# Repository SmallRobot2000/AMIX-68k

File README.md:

# AMIX-68k
This is my Motorola 68010 CPU based system.
I plan to make it with 68010 CPU @ 12Mhz, DMA(68450) and othere periferials @ 10Mhz, IDE disk (CF card or good old HDD), Video output (Xosera), Aduio output (Aslo Xosera), Timers (again Xosera and 68230), Keyboard (68230 with RC2014 Yellow series MSX style keyboard), UART (16550 @ 115200 bps)

This isn't my first or (hopefully)last Retro style computer system, I alredy made two 6502 based computers, 8088 based system that is IBM compatable with 8 bit ISA, and built and coded for a handfull of z80/z180 based systems, mostly two RC2014 (Its funny that i like z80 MUCH more than 6502 but never made a system araund z80).
And also have ZX Spectrum 48k and ZX Spectrum NEXT.

But somehow this is the first time working with 68k chip, I known for 68k style systems but was afraid to touch them because they are two times more complex thatn 8 bit(right?) especely when i made 8088 system that was 8/16 bit and coudnt think how complecated would a full 16 bit system be, but when i looked closer at Motorola 68000 i thought i steped in to heven because of all the documentation and datasheet, and how a SINGLE datasheet was enough to understand almost everything to know(looking at you Intel).

# SPECS

|CPU | Motorola 68010 @ 12Mhz|
|----|-----------------------|
|RAM | 2 MB SRAM (Maybe DRAM in future)
|DMA | 68450 @ 10 Mhz|
|VIDEO & AUDIO| Xosera 640x480 2 playfields and Copper ( ͡❛ ͜ʖ ͡❛)|
|Keyboard| RC2014 Yellow series MSX style keyboard with n key rollover|
|DISK| IDE interface CF card or clasic HDD|
|UART| 16550 @ 18.432 Mhz -> 115200 bps|
|POWER| ATX PSU or 12V in|
|TIME & TIMERS| Tmers in Xosera and 68230, and RTC (SparkFun BOB-10160)|

# Present
All important stuff in kernel is done, now its time to make a unix like shell inside the kernel, later I will make it a executable file
All executables are in ELF file format, scripts are not yet suported nether are pipes and redirects.
# Future (TODO)

 - Add working permissions and thus users
 - Shell as executable not built in kenrel
 - Support for pipes and redirects
 - Move keyboard to a new process and make it all in C because now it sometimes glitches
 - Clean up code and make more flexiable(cariables insted of defines)
 - Move some stuff to files like history and $PATH etc.
 - Add global sbrk with suport for freeing all alocations per process when killed
 - When poritng keyboard to C add some shortcuts
 - add system specific command something similar to symctl
 - add Ethernet as expantion

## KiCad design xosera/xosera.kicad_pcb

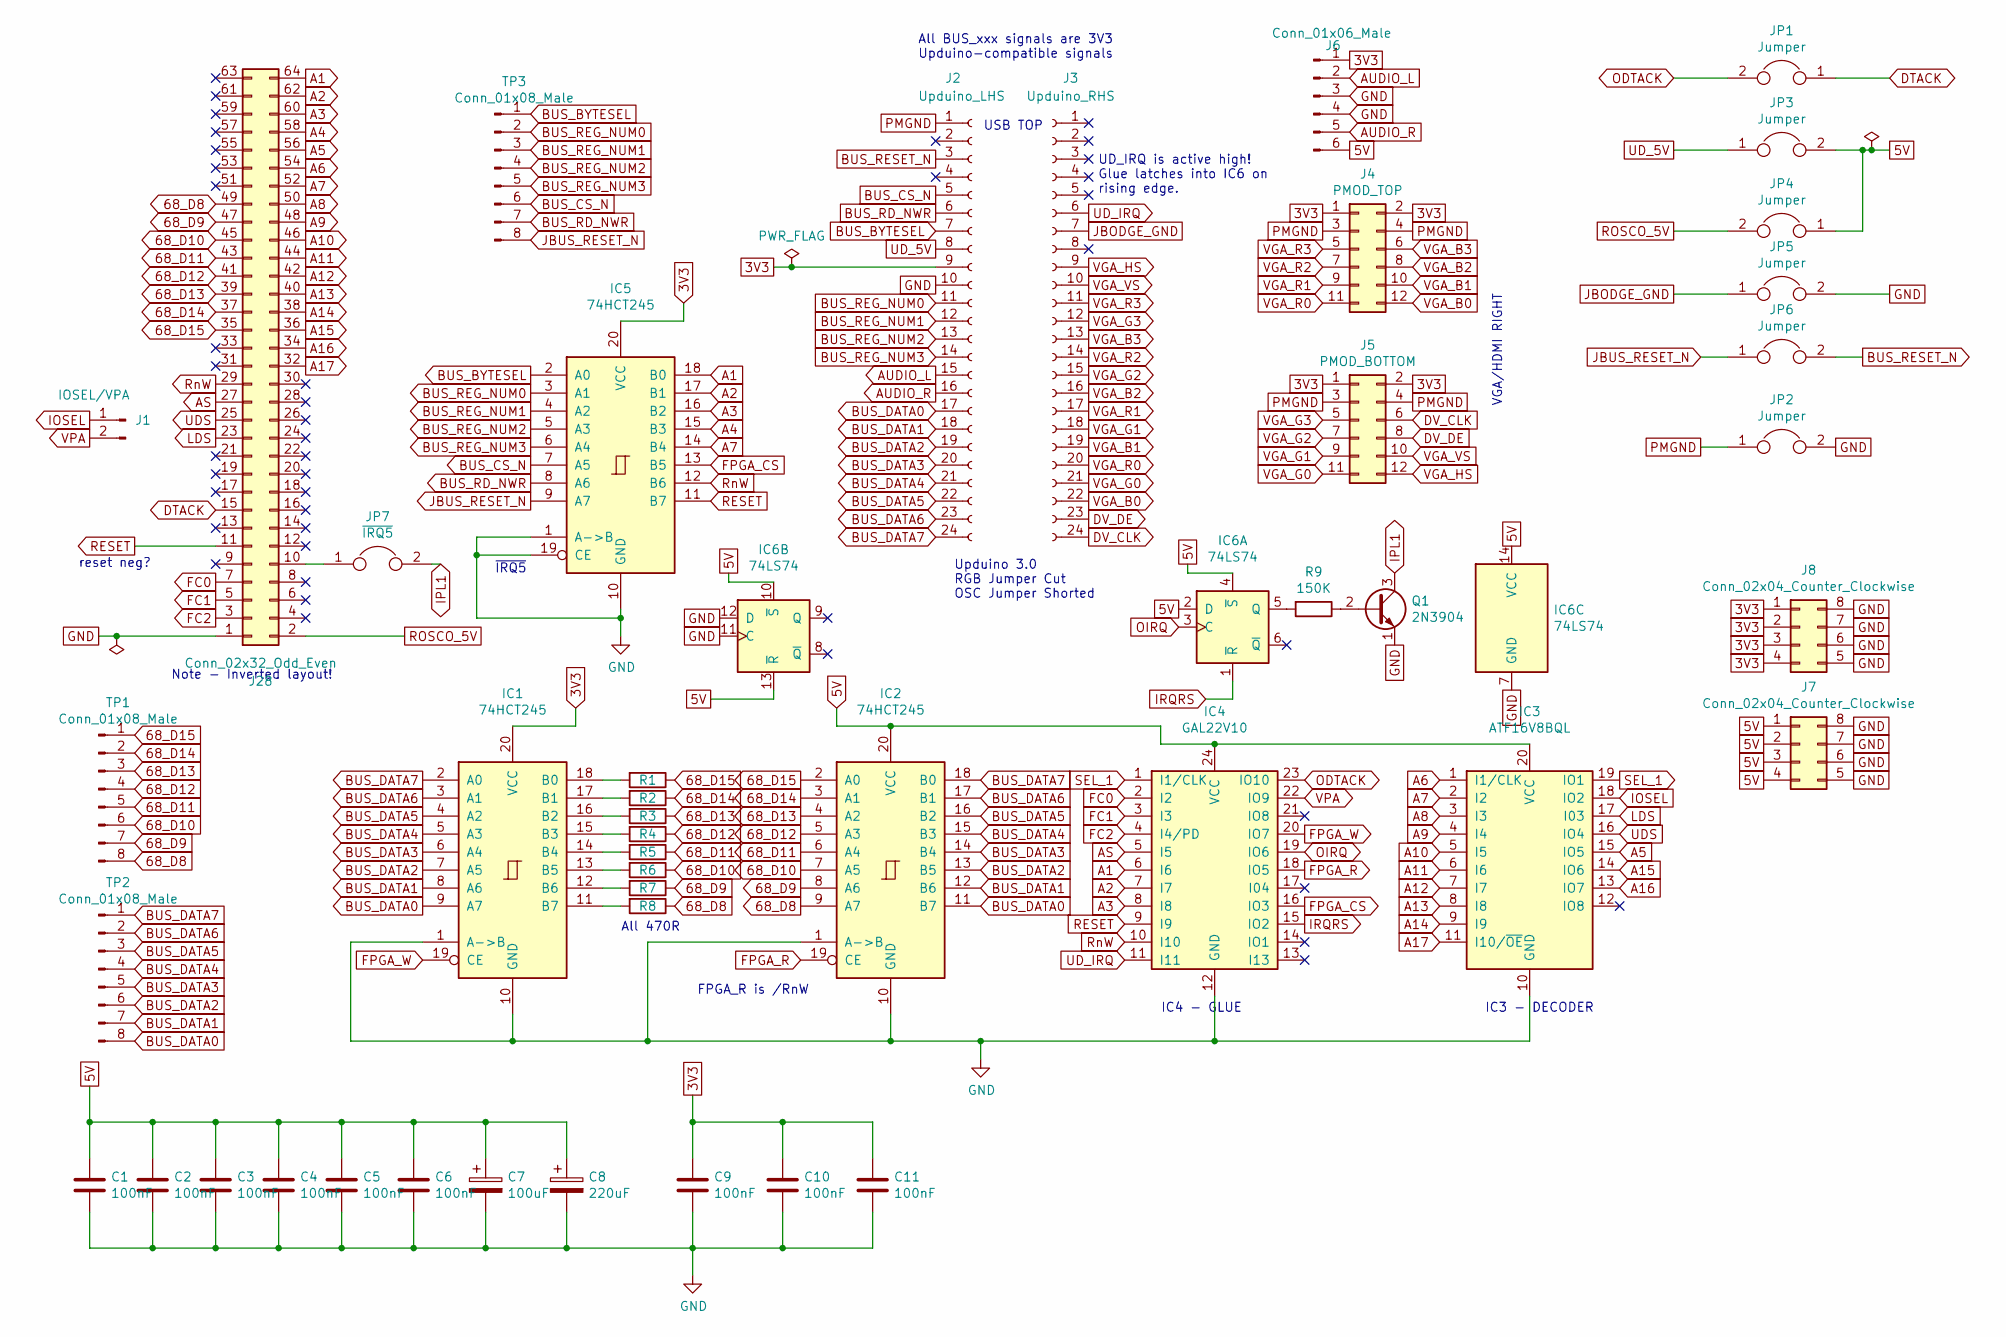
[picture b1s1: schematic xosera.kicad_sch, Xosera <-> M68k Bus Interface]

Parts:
C1, C2, C3, C4, C5, C6, C9, C10, C11: 100nF; C2.5-3
C7: 100uF; CP_Radial_D5.0mm_P2.50mm
C8: 220uF; CP_Radial_D6.3mm_P2.50mm
IC1, IC2, IC5: 74HCT245; DIP-20_W7.62mm_Socket_LongPads
IC3: ATF16V8BQL; DIP-20_W7.62mm_Socket_LongPads
IC4: GAL22V10; DIP-24_W7.62mm_LongPads
IC6: 74LS74; DIP-14_W7.62mm_Socket_LongPads
J1: IOSEL/VPA; PinHeader_1x02_P2.54mm_Vertical
J2: Upduino_LHS; PinSocket_1x24_P2.54mm_Vertical
J3: Upduino_RHS; PinSocket_1x24_P2.54mm_Vertical
J4: PMOD_TOP; PinSocket_2x06_P2.54mm_Horizontal
J5: PMOD_BOTTOM; PinSocket_2x06_P2.54mm_Horizontal
J6: Conn_01x06_Male; PinHeader_1x06_P2.54mm_Vertical
J7, J8: Conn_02x04_Counter_Clockwise; PinHeader_2x04_P2.54mm_Vertical
J28: Conn_02x32_Odd_Even; PinSocket_2x32_P2.54mm_Horizontal
JP1, JP3, JP4, JP5, JP6: Jumper; PinHeader_1x02_P2.54mm_Vertical
JP2: Jumper; SolderJumper-2_P1.3mm_Open_Pad1.0x1.5mm
JP7: ~{IRQ5}; SolderJumper-2_P1.3mm_Open_Pad1.0x1.5mm
Q1: 2N3904; TO-92_HandSolder
R1, R2, R3, R4, R5, R6, R7, R8: R; R-0207_10
R9: 150K; R-0207_10
TP1, TP2, TP3: Conn_01x08_Male; PinHeader_1x08_P2.54mm_Vertical

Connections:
3V3: C9.1, C10.1, C11.1, IC1.20 (VCC), IC5.20 (VCC), J2.9, J4.1, J4.2, J5.1, J5.2, J6.1, J8.1, J8.2, J8.3, J8.4
68_D8: IC2.9 (A7), J28.49, R8.1, TP1.8
68_D9: IC2.8 (A6), J28.47, R7.1, TP1.7
68_D10: IC2.7 (A5), J28.45, R6.1, TP1.6
68_D11: IC2.6 (A4), J28.43, R5.1, TP1.5
68_D12: IC2.5 (A3), J28.41, R4.1, TP1.4
68_D13: IC2.4 (A2), J28.39, R3.1, TP1.3
68_D14: IC2.3 (A1), J28.37, R2.1, TP1.2
68_D15: IC2.2 (A0), J28.35, R1.1, TP1.1
A1: IC4.6 (I6), IC5.18 (B0), J28.64
A2: IC4.7 (I7), IC5.17 (B1), J28.62
A3: IC4.8 (I8), IC5.16 (B2), J28.60
A4: IC5.15 (B3), J28.58
A5: IC3.15 (IO5), J28.56
A6: IC3.1 (I1/CLK), J28.54
A7: IC3.2 (I2), IC5.14 (B4), J28.52
A8: IC3.3 (I3), J28.50
A9: IC3.4 (I4), J28.48
A10: IC3.5 (I5), J28.46
A11: IC3.6 (I6), J28.44
A12: IC3.7 (I7), J28.42
A13: IC3.8 (I8), J28.40
A14: IC3.9 (I9), J28.38
A15: IC3.14 (IO6), J28.36
A16: IC3.13 (IO7), J28.34
A17: IC3.11 (I10/~OE), J28.32
AS: IC4.5 (I5), J28.27
AUDIO_L: J2.15, J6.2
AUDIO_R: J2.16, J6.5
BUS_BYTESEL: IC5.2 (A0), J2.7, TP3.1
BUS_CS_N: IC5.7 (A5), J2.5, TP3.6
BUS_DATA0: IC1.9 (A7), IC2.11 (B7), J2.17, TP2.8
BUS_DATA1: IC1.8 (A6), IC2.12 (B6), J2.18, TP2.7
BUS_DATA2: IC1.7 (A5), IC2.13 (B5), J2.19, TP2.6
BUS_DATA3: IC1.6 (A4), IC2.14 (B4), J2.20, TP2.5
BUS_DATA4: IC1.5 (A3), IC2.15 (B3), J2.21, TP2.4
BUS_DATA5: IC1.4 (A2), IC2.16 (B2), J2.22, TP2.3
BUS_DATA6: IC1.3 (A1), IC2.17 (B1), J2.23, TP2.2
BUS_DATA7: IC1.2 (A0), IC2.18 (B0), J2.24, TP2.1
BUS_RD_NWR: IC5.8 (A6), J2.6, TP3.7
BUS_REG_NUM0: IC5.3 (A1), J2.11, TP3.2
BUS_REG_NUM1: IC5.4 (A2), J2.12, TP3.3
BUS_REG_NUM2: IC5.5 (A3), J2.13, TP3.4
BUS_REG_NUM3: IC5.6 (A4), J2.14, TP3.5
BUS_RESET_N: J2.3, JP6.2
DTACK: J28.15, JP1.1
DV_CLK: J3.24, J5.6
DV_DE: J3.23, J5.8
FC0: IC4.2 (I2), J28.7
FC1: IC4.3 (I3), J28.5
FC2: IC4.4 (I4/PD), J28.3
FPGA_CS: IC4.16 (IO3), IC5.13 (B5)
FPGA_R: IC2.19 (CE), IC4.18 (IO5)
FPGA_W: IC1.19 (CE), IC4.20 (IO7)
IOSEL: IC3.18 (IO2), J1.1
IPL1: JP7.2, Q1.3 (C)
IRQRS: IC4.15 (IO2), IC6.1 (~R)
JBODGE_GND: J3.7, JP5.1
JBUS_RESET_N: IC5.9 (A7), JP6.1, TP3.8
LDS: IC3.17 (I03), J28.23
unnamed: IC1.18 (B0), R1.2
unnamed: IC1.17 (B1), R2.2
unnamed: IC1.16 (B2), R3.2
unnamed: IC1.15 (B3), R4.2
unnamed: IC1.14 (B4), R5.2
unnamed: IC1.13 (B5), R6.2
unnamed: IC1.12 (B6), R7.2
unnamed: IC1.11 (B7), R8.2
unnamed: IC6.5 (Q), R9.2
unnamed: J28.10, JP7.1
unnamed: Q1.2 (B), R9.1
ODTACK: IC4.23 (IO10), JP1.2
OIRQ: IC4.19 (IO6), IC6.3 (C)
PMGND: J2.1, J4.3, J4.4, J5.3, J5.4, JP2.1
RESET: IC4.9 (I9), IC5.11 (B7), J28.11
ROSCO_5V: J28.2, JP4.2
RnW: IC4.10 (I10), IC5.12 (B6), J28.29
SEL_1: IC3.19 (IO1), IC4.1 (I1/CLK)
UDS: IC3.16 (IO4), J28.25
UD_5V: J2.8, JP3.1
UD_IRQ: IC4.11 (I11), J3.6
VGA_B0: J3.22, J4.12
VGA_B1: J3.19, J4.10
VGA_B2: J3.16, J4.8
VGA_B3: J3.13, J4.6
VGA_G0: J3.21, J5.11
VGA_G1: J3.18, J5.9
VGA_G2: J3.15, J5.7
VGA_G3: J3.12, J5.5
VGA_HS: J3.9, J5.12
VGA_R0: J3.20, J4.11
VGA_R1: J3.17, J4.9
VGA_R2: J3.14, J4.7
VGA_R3: J3.11, J4.5
VGA_VS: J3.10, J5.10
VPA: IC4.22 (IO9), J1.2

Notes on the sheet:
All BUS_xxx signals are 3V3 Upduino-compatible signals
VGA/HDMI RIGHT
~{IRQ5}
USB TOP
IC3 - DECODER
FPGA_R is /RnW
All 470R
reset neg?
Note - Inverted layout!
UD_IRQ is active high! Glue latches into IC6 on rising edge.
Upduino 3.0 RGB Jumper Cut OSC Jumper Shorted
IC4 - GLUE

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
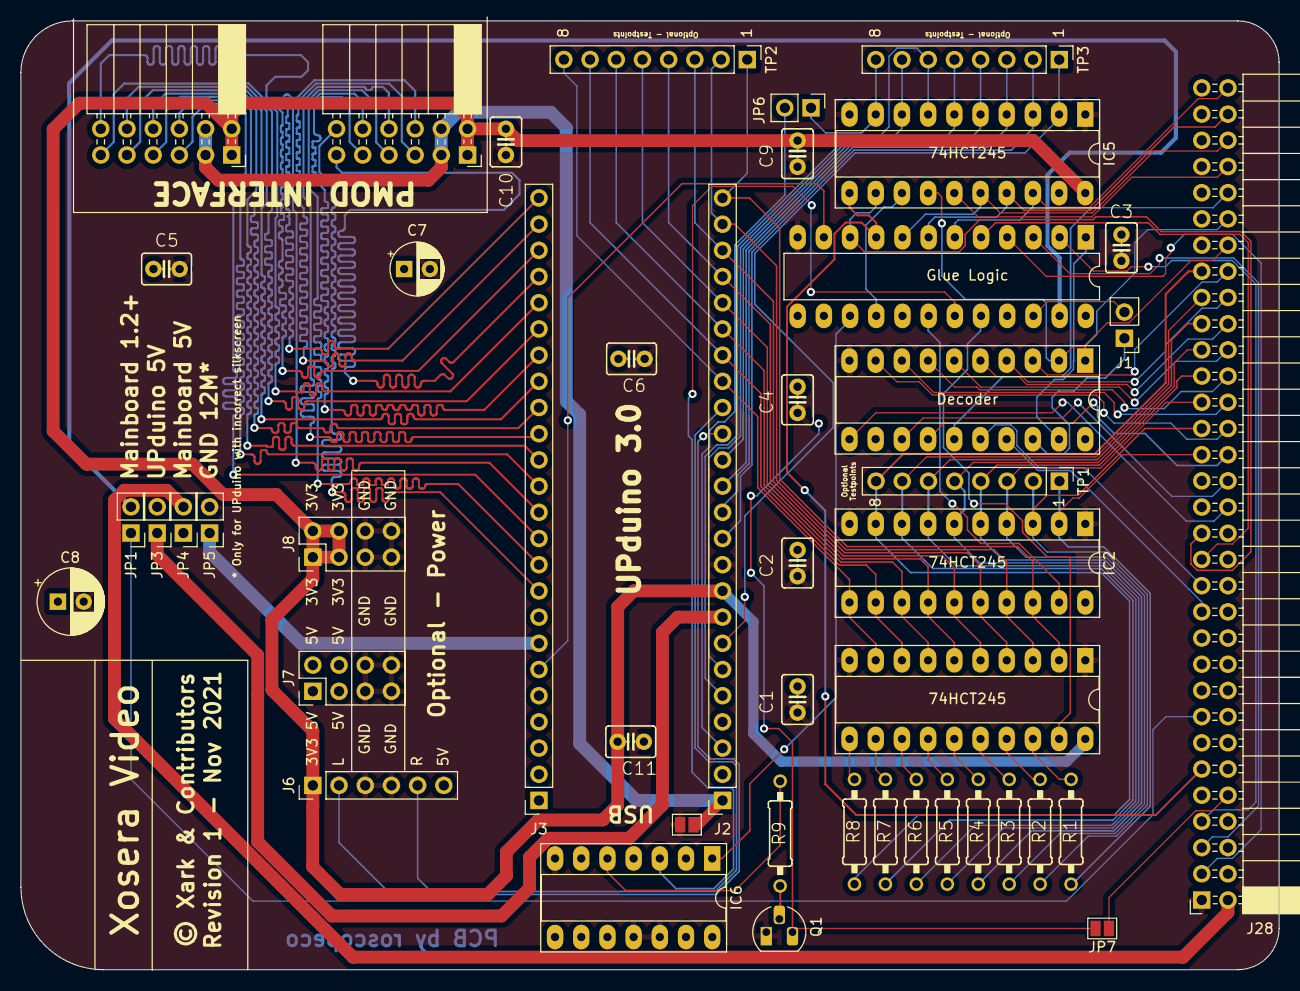
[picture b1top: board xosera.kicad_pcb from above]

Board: 4 copper layers, 122.0 x 92.0 mm, 46 parts (0 on the bottom side), 98 nets.

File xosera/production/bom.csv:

Designator,Footprint,Quantity,Value,LCSC Part #
"C1, C10, C11, C2, C3, C4, C5, C6, C9",C2.5-3,9,100nF,
C7,CP_Radial_D5.0mm_P2.50mm,1,100uF,
C8,CP_Radial_D6.3mm_P2.50mm,1,220uF,
"IC1, IC2, IC5",DIP-20_W7.62mm_Socket_LongPads,3,74HCT245,
IC3,DIP-20_W7.62mm_Socket_LongPads,1,ATF16V8BQL,
IC4,DIP-24_W7.62mm_LongPads,1,GAL22V10,
IC6,DIP-14_W7.62mm_Socket_LongPads,1,74LS74,
J1,PinHeader_1x02_P2.54mm_Vertical,1,IOSEL/VPA,
J2,PinSocket_1x24_P2.54mm_Vertical,1,Upduino_LHS,
J28,PinSocket_2x32_P2.54mm_Horizontal,1,Conn_02x32_Odd_Even,
J3,PinSocket_1x24_P2.54mm_Vertical,1,Upduino_RHS,
J4,PinSocket_2x06_P2.54mm_Horizontal,1,PMOD_TOP,
J5,PinSocket_2x06_P2.54mm_Horizontal,1,PMOD_BOTTOM,
J6,PinHeader_1x06_P2.54mm_Vertical,1,Conn_01x06_Male,
"J7, J8",PinHeader_2x04_P2.54mm_Vertical,2,Conn_02x04_Counter_Clockwise,
"JP1, JP3, JP4, JP5, JP6",PinHeader_1x02_P2.54mm_Vertical,5,Jumper,
JP2,SolderJumper-2_P1.3mm_Open_Pad1.0x1.5mm,1,Jumper,
JP7,SolderJumper-2_P1.3mm_Open_Pad1.0x1.5mm,1,~{IRQ5},
Q1,TO-92_HandSolder,1,2N3904,
"R1, R2, R3, R4, R5, R6, R7, R8",R-0207_10,8,R,
R9,R-0207_10,1,150K,
"TP1, TP2, TP3",PinHeader_1x08_P2.54mm_Vertical,3,Conn_01x08_Male,

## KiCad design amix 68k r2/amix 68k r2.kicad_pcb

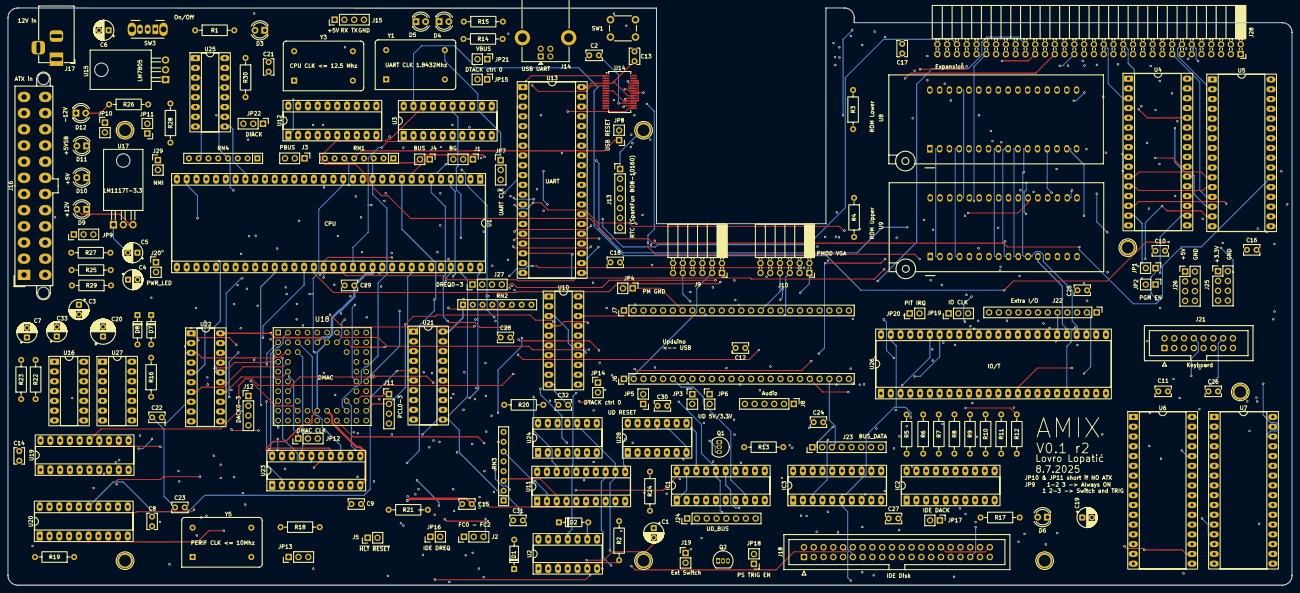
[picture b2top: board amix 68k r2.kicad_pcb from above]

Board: 4 copper layers, 333.4 x 149.9 mm, 175 parts (0 on the bottom side), 269 nets.

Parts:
C1: C_Polarized; CP_Radial_D5.0mm_P2.50mm
C2: 1uF; C_Rect_L4.0mm_W2.5mm_P2.50mm
C3, C5, C7: 10uF; CP_Radial_D5.0mm_P2.50mm
C4, C6, C33: 1uF; CP_Radial_D5.0mm_P2.50mm
C8, C9, C10, C11, C12, C13, C14, C15, C16, C17, C18, C21, C22, C23, C24, C25, C26, C27, C28, C29, C30, C31, C32: 100nF; C_Rect_L4.0mm_W2.5mm_P2.50mm
C19: 100uF; CP_Radial_D5.0mm_P2.50mm
C20: 220uF; CP_Radial_D6.3mm_P2.50mm
D1, D2: D; D_DO-35_SOD27_P7.62mm_Horizontal
D3, D4, D5, D6: LED; LED_D4.0mm
D7, D8: 1N4148; D_DO-35_SOD27_P7.62mm_Horizontal
D9: LED_+12; LED_D4.0mm
D10: LED_+5; LED_D4.0mm
D11: LED_+5SB; LED_D4.0mm
D12: LED_-12; LED_D4.0mm
HOLE1, HOLE2, HOLE3, HOLE4, HOLE5, HOLE6, HOLE7: HOLE; Hole_3mm
IC1, IC2, IC3: 74HCT245; DIP-20_W7.62mm_Socket_LongPads
J1: BG; PinHeader_1x03_P2.54mm_Vertical
J2: FCx; PinHeader_1x03_P2.54mm_Vertical
J3: PRF; PinHeader_1x03_P2.54mm_Vertical
J4: BUS_STAT; PinHeader_1x02_P2.54mm_Vertical
J5: HLT and RESET; PinHeader_1x02_P2.54mm_Vertical
J6: Upduino_LHS; PinHeader_1x24_P2.54mm_Vertical
J7: Upduino_RHS; PinHeader_1x24_P2.54mm_Vertical
J8: Conn_01x06_Pin; PinHeader_1x06_P2.54mm_Vertical
J9: PMOD_TOP; PinSocket_2x06_P2.54mm_Horizontal
J10: PMOD_BOTTOM; PinSocket_2x06_P2.54mm_Horizontal
J11, J12, J15, J27: Conn_01x04_Pin; PinHeader_1x04_P2.54mm_Vertical
J13: RTC (SparkFun BOB-10160); PinHeader_1x07_P2.54mm_Vertical
J14: USB_B; USB_B_Lumberg_2411_02_Horizontal
J16: ATX-24 - IF NO 12V in; Molex_Mini-Fit_Jr_5566-24A2_2x12_P4.20mm_Vertical
J17: 12V in if NO ATX; BarrelJack_Horizontal
J18: IDE 40 pin; IDC-Header_2x20_P2.54mm_Vertical
J19: ExtPWRON; PinHeader_1x02_P2.54mm_Vertical
J20: PWR_LED; PinHeader_1x02_P2.54mm_Vertical
J21: Conn_02x08_Odd_Even; IDC-Header_2x08_P2.54mm_Vertical
J22: PPI; PinHeader_1x12_P2.54mm_Vertical
J23, J24: Conn_01x08_Pin; PinHeader_1x08_P2.54mm_Vertical
J25, J26: Conn_02x04_Odd_Even; PinHeader_2x04_P2.54mm_Vertical
J28: Conn_02x32_Odd_Even; PinSocket_2x32_P2.54mm_Horizontal
J29: NMI; PinHeader_1x02_P2.54mm_Vertical
JP1, JP2, JP8, JP21: Jumper_2_Open; PinHeader_1x02_P2.54mm_Vertical
JP3, JP4, JP5, JP6: Jumper; PinHeader_1x02_P2.54mm_Vertical
JP7, JP19, JP22: Jumper_3_Bridged12; PinHeader_1x03_P2.54mm_Vertical
JP9: 1-2 3 - > Always ON, 1 2-3 -> Enabled On/Off; PinHeader_1x03_P2.54mm_Vertical
JP10, JP11: Close only if NO ATX; PinHeader_1x02_P2.54mm_Vertical
JP12: DMAC CLK; PinHeader_1x03_P2.54mm_Vertical
JP13: DTACK_Pull UP/DOWN; PinHeader_1x03_P2.54mm_Vertical
JP14, JP15: DTACK ctrl 0; PinHeader_1x02_P2.54mm_Vertical
JP16: DMAAC_REQ0 = IDE; PinHeader_1x02_P2.54mm_Vertical
JP17: DMAAC_ACK0 = IDE; PinHeader_1x02_P2.54mm_Vertical
JP18, JP20: Jumper_2_Bridged; PinHeader_1x02_P2.54mm_Vertical
Q1, Q2: 2N3904; TO-92_Inline
R1, R2, R14, R15, R17: 1k; R_Axial_DIN0207_L6.3mm_D2.5mm_P10.16mm_Horizontal
R3, R4, R16, R18, R19, R20, R21, R22, R30: 10k; R_Axial_DIN0207_L6.3mm_D2.5mm_P10.16mm_Horizontal
R5, R6, R7, R8, R9, R10, R11, R12: R; R_Axial_DIN0207_L6.3mm_D2.5mm_P10.16mm_Horizontal
R13, R24: 150k; R_Axial_DIN0207_L6.3mm_D2.5mm_P10.16mm_Horizontal
R23: 470; R_Axial_DIN0207_L6.3mm_D2.5mm_P10.16mm_Horizontal
R25, R26: 680; R_Axial_DIN0207_L6.3mm_D2.5mm_P10.16mm_Horizontal
R27, R28, R29: 330; R_Axial_DIN0207_L6.3mm_D2.5mm_P10.16mm_Horizontal
RN1, RN2, RN3, RN4: R_Network07; R_Array_SIP8
SW1: Reset; SW_PUSH_6mm
SW3: SW_SPDT; SW_Slide_SPDT_Angled_CK_OS102011MA1Q
U1: MC68010P; DIP-64_W22.86mm_Socket_LongPads
U2, U27: 74HC14; DIP-14_W7.62mm_Socket_LongPads
U3, U10, U11, U12: GAL16V8; DIP-20_W7.62mm_Socket_LongPads
U4, U5, U6, U7: AS6C4008-55PCN; DIP-32_W15.24mm_Socket_LongPads
U8, U9: SST39SF040; DIP_Socket-32_W11.9_W12.7_W15.24_W17.78_W18.5_3M_232-1285-0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
U13: 16550; DIP-40_W15.24mm_Socket_LongPads
U14: FT232RL; SSOP-28_5.3x10.2mm_P0.65mm
U15: LM7805_TO220; TO-220-3_Horizontal_TabDown
U16, U28: 74HC74; DIP-14_W7.62mm_Socket_LongPads
U17: LM1117T-3.3; TO-220-3_Horizontal_TabDown
U18: 68 pin PGA socket 5108306810061101
U19, U20, U21: 74HC245; DIP-20_W7.62mm_Socket_LongPads
U22, U23: 74HC373; DIP-20_W7.62mm_Socket_LongPads
U24: 74LS32; DIP-14_W7.62mm_Socket_LongPads
U25: 74LS148; DIP-16_W7.62mm_Socket_LongPads
U26: 68230; DIP-48_W15.24mm_Socket_LongPads
Y1: 1.8432Mhz; Oscillator_DIP-14
Y3: 12Mhz; Oscillator_DIP-14
Y5: 10Mhz; Oscillator_DIP-14

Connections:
+3.3V: C21.1, C22.1, C23.1, IC1.20 (VCC), IC2.20 (VCC), J8.1, J9.1, J9.2, J10.1, J10.2, J16.1 (+3.3V), J16.2 (+3.3V), J16.12 (+3.3V), J16.13 (+3.3V), J25.1, J25.3, J25.5, J25.7, JP6.2 (B), JP10.1 (A)
+5V: C8.1, C9.1, C10.1, C11.1, C12.1, C13.1, C14.1, C15.1, C16.1, C17.1, C18.1, C19.1, C20.1, C24.1, C25.1, C26.1, C27.1, C28.1, C29.1, C30.1, C31.1, C32.1, D10.2 (A), IC3.20 (VCC), J8.6, J13.2, J15.1, J16.4 (+5V), J16.6 (+5V), J16.21 (+5V), J16.22 (+5V), J16.23 (+5V), J18.20, J18.38, J20.2, J21.2, J26.1, J26.3, J26.5, J26.7, J28.64, JP3.2 (B), JP11.1 (A), JP13.3 (B), JP21.2 (B), R1.1, R2.2, R3.2, R4.2, R14.2, R15.2, R17.2, R19.2, R20.2, R21.2, R30.2, RN1.1 (common), RN2.1 (common), RN3.1 (common), RN4.1 (common), U1.14 (V_{CC}), U1.49 (V_{CC}), U2.14 (VCC), U3.20 (VCC), U4.32 (VCC), U5.32 (VCC), U6.32 (VCC), U7.32 (VCC), U8.32 (VCC), U9.32 (VCC), U10.20 (VCC), U11.20 (VCC), U12.20 (VCC), U13.12 (CS0), U13.13 (CS1), U13.40 (VCC), U14.4 (VCCIO), U14.20 (VCC), U18.B6 (VCC), U18.J5 (Vcc), U19.20 (VCC), U20.20 (VCC), U21.20 (VCC), U22.20 (VCC), U23.20 (VCC), U24.14 (VCC), U25.16 (VCC), U26.12 (VCC), U28.1 (~R), U28.2 (D), U28.4 (~S), U28.10 (~S), U28.13 (~R), U28.14 (VCC), Y1.14 (Vcc), Y3.14 (Vcc), Y5.14 (Vcc)
+5VSB: D7.1 (K), D8.1 (K), D11.2 (A), J16.9 (+5VSB), R16.1, R22.1, U16.1 (~R), U16.10 (~S), U16.11 (C), U16.12 (D), U16.13 (~R), U16.14 (VCC), U27.9, U27.11, U27.13, U27.14 (VCC)
+12V: C3.1, C5.1, D9.2 (A), J16.10 (+12V), J16.11 (+12V), J17.1, J28.60, U15.1 (VI), U17.3 (VI)
-12V: D12.1 (K), J16.14 (-12V), J28.62
/UART + RTC + IDE/~IDE_LED: D6.1 (K), J18.39
A0: IC1.18 (B0), U10.15 (IO5)
A1: IC1.17 (B1), J18.35, J28.2, U1.29 (A1), U4.12 (A0), U5.12 (A0), U6.12 (A0), U7.12 (A0), U8.12 (A0), U9.12 (A0), U10.5 (I5), U13.28 (A0), U18.C8 (A1), U26.29 (RS1)
A2: IC1.16 (B2), J18.33, J28.4, U1.30 (A2), U4.11 (A1), U5.11 (A1), U6.11 (A1), U7.11 (A1), U8.11 (A1), U9.11 (A1), U13.27 (A1), U18.B8 (A2), U26.28 (RS2)
A3: IC1.15 (B3), J18.36, J28.6, U1.31 (A3), U4.10 (A2), U5.10 (A2), U6.10 (A2), U7.10 (A2), U8.10 (A2), U9.10 (A2), U13.26 (A2), U18.A9 (A3), U26.27 (RS3)
A4: IC1.14 (B4), J28.8, U1.32 (A4), U4.9 (A3), U5.9 (A3), U6.9 (A3), U7.9 (A3), U8.9 (A3), U9.9 (A3), U18.B7 (A4), U26.26 (RS4)
A5: J28.10, U1.33 (A5), U4.8 (A4), U5.8 (A4), U6.8 (A4), U7.8 (A4), U8.8 (A4), U9.8 (A4), U18.A8 (A5), U26.25 (RS5)
A6: J28.12, U1.34 (A6), U4.7 (A5), U5.7 (A5), U6.7 (A5), U7.7 (A5), U8.7 (A5), U9.7 (A5), U18.A7 (A6)
A7: J28.14, U1.35 (A7), U4.6 (A6), U5.6 (A6), U6.6 (A6), U7.6 (A6), U8.6 (A6), U9.6 (A6), U18.A6 (A7)
A8: J28.16, U1.36 (A8), U4.5 (A7), U5.5 (A7), U6.5 (A7), U7.5 (A7), U8.5 (A7), U9.5 (A7), U23.2 (O0)
A9: J28.18, U1.37 (A9), U4.27 (A8), U5.27 (A8), U6.27 (A8), U7.27 (A8), U8.27 (A8), U9.27 (A8), U23.5 (O1)
A10: J28.20, U1.38 (A10), U4.26 (A9), U5.26 (A9), U6.26 (A9), U7.26 (A9), U8.26 (A9), U9.26 (A9), U23.6 (O2)
A11: J28.22, U1.39 (A11), U4.23 (A10), U5.23 (A10), U6.23 (A10), U7.23 (A10), U8.23 (A10), U9.23 (A10), U23.9 (O3)
A12: J28.24, U1.40 (A12), U4.25 (A11), U5.25 (A11), U6.25 (A11), U7.25 (A11), U8.25 (A11), U9.25 (A11), U11.5 (I5), U23.12 (O4)
A13: J28.26, U1.41 (A13), U4.4 (A12), U5.4 (A12), U6.4 (A12), U7.4 (A12), U8.4 (A12), U9.4 (A12), U11.6 (I6), U23.15 (O5)
A14: J28.28, U1.42 (A14), U4.28 (A13), U5.28 (A13), U6.28 (A13), U7.28 (A13), U8.28 (A13), U9.28 (A13), U11.7 (I7), U23.16 (O6)
A15: J28.30, U1.43 (A15), U4.3 (A14), U5.3 (A14), U6.3 (A14), U7.3 (A14), U8.29 (A14), U9.29 (A14), U11.8 (I8), U23.19 (O7)
A16: J28.32, U1.44 (A16), U4.31 (A15), U5.31 (A15), U6.31 (A15), U7.31 (A15), U8.3 (A15), U9.3 (A15), U11.9 (I9), U22.2 (O0)
A17: J28.34, U1.45 (A17), U4.2 (A16), U5.2 (A16), U6.2 (A16), U7.2 (A16), U8.2 (A16), U9.2 (A16), U11.11 (I10/~OE), U22.5 (O1)
A18: J28.36, U1.46 (A18), U3.1 (I1/CLK), U4.30 (A17), U5.30 (A17), U6.30 (A17), U7.30 (A17), U8.30 (A17), U9.30 (A17), U22.6 (O2)
A19: J28.38, U1.47 (A19), U3.2 (I2), U4.1 (A18), U5.1 (A18), U6.1 (A18), U7.1 (A18), U8.1 (A18), U9.1 (A18), U22.9 (O3)
A20: J28.40, U1.48 (A20), U3.3 (I3), U22.12 (O4)
A21: J28.42, U1.50 (A21), U3.4 (I4), U22.15 (O5)
A22: J28.44, U1.51 (A22), U3.5 (I5), U22.16 (O6)
A23: J28.46, U1.52 (A23), U3.6 (I6), U22.19 (O7)
AUDIO_L: J6.15, J8.5
AUDIO_R: J6.16, J8.2
BUS_BYTESEL: IC1.2 (A0), J6.7, J24.1
BUS_CS_N: IC1.7 (A5), J6.5, J24.6
BUS_DATA0: IC2.9 (A7), IC3.11 (B7), J6.17, J23.8
BUS_DATA1: IC2.8 (A6), IC3.12 (B6), J6.18, J23.7
BUS_DATA2: IC2.7 (A5), IC3.13 (B5), J6.19, J23.6
BUS_DATA3: IC2.6 (A4), IC3.14 (B4), J6.20, J23.5
BUS_DATA4: IC2.5 (A3), IC3.15 (B3), J6.21, J23.4
BUS_DATA5: IC2.4 (A2), IC3.16 (B2), J6.22, J23.3
BUS_DATA6: IC2.3 (A1), IC3.17 (B1), J6.23, J23.2
BUS_DATA7: IC2.2 (A0), IC3.18 (B0), J6.24, J23.1
BUS_RD_NWR: IC1.8 (A6), J6.6, J24.7
BUS_REG_NUM0: IC1.3 (A1), J6.11, J24.2
BUS_REG_NUM1: IC1.4 (A2), J6.12, J24.3
BUS_REG_NUM2: IC1.5 (A3), J6.13, J24.4
BUS_REG_NUM3: IC1.6 (A4), J6.14, J24.5
BUS_RESET_N: J6.3, JP5.2 (B)
CLK: J28.31, JP12.3 (B), JP19.3 (B), U1.15 (CLK), Y3.8 (OUT)
D0: J18.4, U1.5 (D0), U4.13 (DQ0), U6.13 (DQ0), U8.13 (D0), U19.18 (B0), U21.18 (B0)
D1: J18.6, J28.1, U1.4 (D1), U4.14 (DQ1), U6.14 (DQ1), U8.14 (D1), U19.17 (B1), U21.17 (B1)
D2: J18.8, J28.3, U1.3 (D2), U4.15 (DQ2), U6.15 (DQ2), U8.15 (D2), U19.16 (B2), U21.16 (B2)
D3: J18.10, J28.5, U1.2 (D3), U4.17 (DQ3), U6.17 (DQ3), U8.17 (D3), U19.15 (B3), U21.15 (B3)
D4: J18.12, J28.7, U1.1 (D4), U4.18 (DQ4), U6.18 (DQ4), U8.18 (D4), U19.14 (B4), U21.14 (B4)
D5: J18.14, J28.9, U1.64 (D5), U4.19 (DQ5), U6.19 (DQ5), U8.19 (D5), U19.13 (B5), U21.13 (B5)
D6: J18.16, J28.11, U1.63 (D6), U4.20 (DQ6), U6.20 (DQ6), U8.20 (D6), U19.12 (B6), U21.12 (B6)
D7: J18.18, J28.13, U1.62 (D7), U4.21 (DQ7), U6.21 (DQ7), U8.21 (D7), U19.11 (B7), U21.11 (B7)
D8: IC3.9 (A7), J18.17, J28.15, R12.2, U1.61 (D8), U5.13 (DQ0), U7.13 (DQ0), U9.13 (D0), U13.1 (D0), U20.18 (B0), U21.2 (A0), U26.44 (D0)
D9: IC3.8 (A6), J18.15, J28.17, R11.2, U1.60 (D9), U5.14 (DQ1), U7.14 (DQ1), U9.14 (D1), U13.2 (D1), U20.17 (B1), U21.3 (A1), U26.45 (D1)
D10: IC3.7 (A5), J18.13, J28.19, R10.2, U1.59 (D10), U5.15 (DQ2), U7.15 (DQ2), U9.15 (D2), U13.3 (D2), U20.16 (B2), U21.4 (A2), U26.46 (D2)
D11: IC3.6 (A4), J18.11, J28.21, R9.2, U1.58 (D11), U5.17 (DQ3), U7.17 (DQ3), U9.17 (D3), U13.4 (D3), U20.15 (B3), U21.5 (A3), U26.47 (D3)
D12: IC3.5 (A3), J18.9, J28.23, R8.2, U1.57 (D12), U5.18 (DQ4), U7.18 (DQ4), U9.18 (D4), U13.5 (D4), U20.14 (B4), U21.6 (A4), U26.48 (D4)
D13: IC3.4 (A2), J18.7, J28.25, R7.2, U1.56 (D13), U5.19 (DQ5), U7.19 (DQ5), U9.19 (D5), U13.6 (D5), U20.13 (B5), U21.7 (A5), U26.1 (D5)
D14: IC3.3 (A1), J18.5, J28.27, R6.2, U1.55 (D14), U5.20 (DQ6), U7.20 (DQ6), U9.20 (D6), U13.7 (D6), U20.12 (B6), U21.8 (A6), U26.2 (D6)
D15: IC3.2 (A0), J18.3, J28.29, R5.2, U1.54 (D15), U5.21 (DQ7), U7.21 (DQ7), U9.21 (D7), U13.8 (D7), U20.11 (B7), U21.9 (A7), U26.3 (D7)
DMAC_A8/D0: U18.A5 (A8/D0), U19.2 (A0), U23.3 (D0)
DMAC_A9/D1: U18.B4 (A9/D1), U19.3 (A1), U23.4 (D1)
DMAC_A10/D2: U18.A4 (A10/D2), U19.4 (A2), U23.7 (D2)
DMAC_A11/D3: U18.A3 (A11/D3), U19.5 (A3), U23.8 (D3)
DMAC_A12/D4: U18.B3 (A12/D4), U19.6 (A4), U23.13 (D4)
DMAC_A13/D5: U18.A2 (A13/D5), U19.7 (A5), U23.14 (D5)
DMAC_A14/D6: U18.C3 (A14/D6), U19.8 (A6), U23.17 (D6)
DMAC_A15/D7: U18.B2 (A15/D7), U19.9 (A7), U23.18 (D7)
DMAC_A16/D8: U18.C2 (A16/D8), U20.2 (A0), U22.3 (D0)
DMAC_A17/D9: U18.B1 (A17/D9), U20.3 (A1), U22.4 (D1)
DMAC_A18/D10: U18.D2 (A18/D10), U20.4 (A2), U22.7 (D2)
DMAC_A19/D11: U18.C1 (A19/D11), U20.5 (A3), U22.8 (D3)
DMAC_A20/D12: U18.D1 (A20/D12), U20.6 (A4), U22.13 (D4)
DMAC_A21/D13: U18.E2 (A21/D13), U20.7 (A5), U22.14 (D5)
DMAC_A22/D14: U18.E1 (A22/D14), U20.8 (A6), U22.17 (D6)
DMAC_A23/D15: U18.F1 (A23/D15), U20.9 (A7), U22.18 (D7)
DMAC_PCL0: J11.1, U18.H9 (PCL0)
DMAC_PCL1: J11.2, J28.54, U18.J10 (PCL1)
DMAC_PCL2: J11.3, U18.G9 (PCL2)
DMAC_PCL3: J11.4, U18.H10 (PCL3)
DV_CLK: J7.24, J10.6
DV_DE: J7.23, J10.8
E: J3.2, J28.55, U1.20 (E)
FC0: J2.1, J28.57, U1.28 (FC0), U12.5 (I5), U18.F2 (FC0)
FC1: J2.2, J28.59, U1.27 (FC1), U12.6 (I6), U18.G1 (FC1)
FC2: J2.3, J28.61, U1.26 (FC2), U12.7 (I7), U18.H1 (FC2)
GND: C1.2, C2.1, C3.2, C4.2, C5.2, C6.2, C7.2, C8.2, C9.2, C10.2, C11.2, C12.2, C13.2, C14.2, C15.2, C16.2, C17.2, C18.2, C19.2, C20.2, C21.2, C22.2, C23.2, C24.2, C25.2, C26.2, C27.2, C28.2, C29.2, C30.2, C31.2, C32.2, C33.2, HOLE1.1, HOLE2.1, HOLE3.1, HOLE4.1, HOLE5.1, HOLE6.1, HOLE7.1, IC1.1 (A->B), IC1.10 (GND), IC1.19 (CE), IC2.1 (A->B), IC2.10 (GND), IC3.1 (A->B), IC3.10 (GND), J6.10, J8.3, J8.4, J13.1, J14.4 (GND), J14.5 (Shield), J15.4, J16.3 (GND), J16.5 (GND), J16.7 (GND), J16.15 (GND), J16.17 (GND), J16.18 (GND), J16.19 (GND), J16.24 (GND), J17.2, J17.3, J18.2, J18.19, J18.22, J18.24, J18.26, J18.30, J18.40, J19.2, J21.16, J25.2, J25.4, J25.6, J25.8, J26.2, J26.4, J26.6, J26.8, J28.63, J29.2, JP4.2 (B), JP9.1 (A), JP13.1 (A), Q1.1 (E), Q2.1 (E), R25.2, R26.2, R27.2, R28.2, R29.2, SW1.2, SW3.2 (B), U1.16 (GND), U1.53 (GND), U2.7 (GND), U3.10 (GND), U4.16 (VSS), U5.16 (VSS), U6.16 (VSS), U7.16 (VSS), U8.16 (GND), U9.16 (GND), U10.10 (GND), U11.10 (GND), U12.10 (GND), U13.19 (WR), U13.20 (GND), U13.22 (RD), U13.25 (~ADS), U14.7 (GND), U14.18 (GND), U14.21 (GND), U14.25 (AGND), U14.26 (TEST), U15.2 (GND), U16.7 (GND), U17.1 (GND), U18.B5 (GND), U18.J6 (GND), U19.10 (GND), U20.10 (GND), U21.10 (GND), U22.10 (GND), U23.10 (GND), U24.7 (GND), U25.5 (EI), U25.8 (GND), U26.38 (GND), U27.7 (GND), U28.7 (GND), U28.11 (C), U28.12 (D), Y1.7 (GND), Y3.7 (GND), Y5.7 (GND)
IO/~M: U3.13 (IO7), U11.1 (I1/CLK)
IRQ_UART: U2.11, U13.30 (INTR)
JBODGE_GND: J7.7, JP4.1 (A)
JBUS_RESET_N: IC1.9 (A7), J24.8, JP5.1 (A)
KYBD_CAPS_LED: J21.12, U26.21 (PB4)
KYBD_CODE_LED: J21.14, U26.22 (PB5)
KYBD_COL_0: J21.1, U26.4 (PA0)
KYBD_COL_1: J21.3, U26.5 (PA1)
KYBD_COL_2: J21.5, U26.6 (PA2)
KYBD_COL_3: J21.7, U26.7 (PA3)
KYBD_COL_4: J21.9, U26.8 (PA4)
KYBD_COL_5: J21.11, U26.9 (PA5)
KYBD_COL_6: J21.13, U26.10 (PA6)
KYBD_COL_7: J21.15, U26.11 (PA7)
KYBD_ROW_A: J21.4, U26.17 (PB0)
KYBD_ROW_B: J21.6, U26.18 (PB1)
KYBD_ROW_C: J21.8, U26.19 (PB2)
KYBD_ROW_D: J21.10, U26.20 (PB3)
unnamed: C1.1, R2.1, SW1.1, U2.3
unnamed: D1.1 (K), D2.1 (K), U2.2
unnamed: D3.2 (A), R1.2
unnamed: D4.2 (A), R14.1
unnamed: D4.1 (K), U14.23 (CBUS0)
unnamed: D5.2 (A), R15.1
unnamed: D5.1 (K), U14.22 (CBUS1)
unnamed: D6.2 (A), R17.1
unnamed: C7.1, D7.2 (A), R16.2, U27.3
unnamed: C33.1, D8.2 (A), R23.2, U27.1
unnamed: D9.1 (K), R25.1
unnamed: D10.1 (K), R27.1
unnamed: D11.1 (K), R28.1
unnamed: D12.2 (A), R26.1
unnamed: IC2.18 (B0), R5.1
unnamed: IC2.17 (B1), R6.1
unnamed: IC2.16 (B2), R7.1
unnamed: IC2.15 (B3), R8.1
unnamed: IC2.14 (B4), R9.1
unnamed: IC2.13 (B5), R10.1
unnamed: IC2.12 (B6), R11.1
unnamed: IC2.11 (B7), R12.1
unnamed: J14.1 (VBUS), JP21.1 (A)
unnamed: J18.21, U2.13
unnamed: J18.29, JP17.1 (A)
unnamed: J19.1, JP18.2 (B), R22.2, R23.1, SW3.1 (A)
unnamed: J20.1, R29.1
unnamed: J22.1, U26.13 (H1)
unnamed: J22.2, U26.14 (H2)
unnamed: J22.3, U26.15 (H3)
unnamed: J22.4, U26.16 (H4)
unnamed: J22.5, U26.30 (PC0)
unnamed: J22.6, U26.31 (PC1)
unnamed: J22.7, U26.32 (TIN/PC2)
unnamed: J22.8, JP20.1 (A), U26.33 (PC3/TOUT)
unnamed: J22.9, U26.34 (DMAREQ/PC4)
unnamed: J22.10, U26.35 (PC5/PIRQ)
unnamed: J22.11, U26.36 (PC6/PIACK)
unnamed: J22.12, U26.37 (PC7/TIACK)
unnamed: JP7.2 (C), U13.16 (XIN)
unnamed: JP8.2 (B), U14.19 (~RESET)
unnamed: JP9.3 (B), U16.5 (Q)
unnamed: C4.1, JP10.2 (B), U17.2 (VO)
unnamed: C6.1, JP11.2 (B), U15.3 (VO)
unnamed: JP12.2 (C), U18.K4 (CLK)
unnamed: JP13.2 (C), R18.1
unnamed: JP14.1 (A), U10.14 (IO6)
unnamed: JP15.1 (A), U3.12 (IO8)
unnamed: JP16.2 (B), U2.12
unnamed: JP18.1 (A), Q2.3 (C)
unnamed: JP19.2 (C), U26.40 (CLK)
unnamed: JP22.2 (C), U18.K3 (~IACK)
unnamed: Q1.2 (B), R13.2
unnamed: Q2.2 (B), R24.2
unnamed: U2.1, U2.4
unnamed: U13.9 (RCLK), U13.15 (~BAUDOUT)
unnamed: C2.2, U14.17 (3V3OUT)
unnamed: U16.3 (C), U27.2
unnamed: U16.2 (D), U16.6 (~Q)
unnamed: U16.4 (~S), U27.6
unnamed: R20.1, U18.D10 (~DBEN), U19.19 (CE), U20.19 (CE)
unnamed: R19.1, U18.E9 (~DDIR), U19.1 (A->B), U20.1 (A->B)
unnamed: R21.1, U18.D9 (~HIBYTE), U21.19 (CE)
unnamed: U2.6, U22.11 (LE), U23.11 (LE)
unnamed: U27.4, U27.5
unnamed: R13.1, U28.5 (Q)
PCLK: J28.33, JP7.3 (B), JP12.1 (A), JP19.1 (A), Y5.8 (OUT)
PMOD_GND: J6.1, J9.3, J9.4, J10.3, J10.4
PS_TRIG: R24.1, U11.14 (IO6)
RESET: U2.8, U13.35 (MR)
RTC_CIPO: J13.5, U13.38 (~DCD)
RTC_CLK: J13.4, U13.34 (~OUT1)
RTC_COPI: J13.6, U13.33 (~DTR)
RTC_SQW: J13.3, U13.37 (~DSR)
RTC_SS: J13.7, U13.31 (~OUT2)
R/~W: IC1.12 (B6), J28.35, RN3.6 (R5), U1.9 (R/~W), U3.7 (I7), U10.1 (I1/CLK), U11.2 (I2), U18.K7 (R/~W), U21.1 (A->B), U26.43 (R/W)
UART_CLK: JP7.1 (A), Y1.8 (OUT)
UART_RX: J15.2, U13.10 (SIN), U14.1 (TXD)
UART_TX: J15.3, U13.11 (SOUT), U14.5 (RXD)
UD_3V3: J6.9, JP6.1 (A)
UD_5V: J6.8, JP3.1 (A)
UD_IRQ: J7.6, U28.3 (C)
USB_D+: J14.3 (D+), U14.15 (USBD+)
USB_D-: J14.2 (D-), U14.16 (USBD-)
VGA_B0: J7.22, J9.12
VGA_B1: J7.19, J9.10
VGA_B2: J7.16, J9.8
VGA_B3: J7.13, J9.6
VGA_G0: J7.21, J10.11
VGA_G1: J7.18, J10.9
VGA_G2: J7.15, J10.7
VGA_G3: J7.12, J10.5
VGA_HS: J7.9, J10.12
VGA_R0: J7.20, J9.11
VGA_R1: J7.17, J9.9
VGA_R2: J7.14, J9.7
VGA_R3: J7.11, J9.5
VGA_VS: J7.10, J10.10
~AS: J28.37, RN3.4 (R3), U1.6 (~AS), U3.11 (I10/~OE), U10.4 (I4), U18.K8 (~AS)
~BERR: J4.2, J28.47, RN1.8 (R7), U1.22 (~BERR)
~BGACK: J1.1, RN1.3 (R2), U1.12 (~BGACK), U18.J8 (~BGACK)
~BG: J1.2, J28.43, U1.11 (~BG), U18.B9 (~BG)
~BR: J1.3, J28.45, RN1.2 (R1), U1.13 (~BR), U18.B10 (~BR)
~DMAC_ACK0: J12.1, JP17.2 (B), U18.K1 (~ACK0)
~DMAC_ACK1: J12.2, J28.52, U18.H3 (~ACK1)
~DMAC_ACK2: J12.3, U18.J2 (~ACK2)
~DMAC_ACK3: J12.4, U18.K2 (~ACK3)
~DMAC_BEC0: RN2.8 (R7), U18.G2 (~BEC0)
~DMAC_BEC1: RN2.6 (R5), U18.J1 (~BEC1)
~DMAC_BEC2: RN2.7 (R6), U18.H2 (~BEC2)
~DMAC_CS: U11.16 (IO4), U18.K5 (~CS)
~DMAC_IACK: JP22.1 (A), U12.17 (I03)
~DMAC_IRQ: RN4.4 (R3), U12.4 (I4), U18.J3 (~IRQ), U25.13 (I3)
~DMAC_OWN: RN3.8 (R7), U18.C9 (~OWN), U22.1 (OE), U23.1 (OE)
~DMAC_REQ0: J27.1, JP16.1 (A), RN2.2 (R1), U18.G10 (~REQ0)
~DMAC_REQ1: J27.2, J28.50, RN2.3 (R2), U18.F9 (~REQ1)
~DMAC_REQ2: J27.3, RN2.4 (R3), U18.F10 (~REQ2)
~DMAC_REQ3: J27.4, RN2.5 (R4), U18.E10 (~REQ3)
~DMAC_UAS: RN3.7 (R6), U2.5, U18.C10 (~UAS)
~DTACK: J4.1, J28.49, JP14.2 (B), JP15.2 (B), R18.2, U1.10 (~DTACK), U18.K10 (~DTACK), U26.42 (DTACK)
~DTC: RN3.5 (R4), U18.H8 (~DTC)
~FPGA_CS: IC1.13 (B5), U11.19 (IO1), U24.4, U24.9
~FPGA_R: IC3.19 (CE), U24.6
~FPGA_W: IC2.19 (CE), U24.8
~HALT: D1.2 (A), D3.1 (K), J5.1, J28.51, RN1.4 (R3), U1.17 (~HALT)
~IACK: JP22.3 (B), U12.18 (IO2)
~IDE0_CS: J18.37, U11.17 (I03)
~IDE_IRQ: J18.31, RN4.3 (R2), U12.3 (I3), U25.12 (I2)
~IO_R: J18.25, U11.13 (IO7), U24.5
~IO_W: J18.23, U11.12 (IO8), U24.10
~IPL0: U1.25 (~IPL0), U25.9 (S0)
~IPL1: U1.24 (~IPL1), U25.7 (S1)
~IPL2: U1.23 (~IPL2), U25.6 (S2)
~IRQX: Q1.3 (C), RN4.2 (R1), U12.1 (I1/CLK), U25.10 (IO)
~IRQ_5: J28.56, RN4.6 (R5), U25.2 (I5)
~IRQ_6: J28.58, RN4.7 (R6), U25.3 (I6)
~IRQ_7: J29.1, RN4.8 (R7), U25.4 (I7)
~IRQ_PIT: JP20.2 (B), R30.1, RN4.5 (R4), U25.1 (I4)
~IRQ_UART: U2.10, U12.2 (I2), U25.11 (I1)
~LDS: J28.41, RN3.3 (R2), U1.8 (~LDS), U3.8 (I8), U10.2 (I2), U11.3 (I3), U18.J7 (~LDS/DS)
~PGM_L: JP1.2 (B), R3.1, U8.31 (PGM)
~PGM_U: JP2.2 (B), R4.1, U9.31 (PGM)
~PPI_CS: U11.15 (IO5), U26.41 (CS)
~PS_ON: J16.16 (PS_ON#), JP9.2 (C)
~RAM0_L_CS: U3.19 (IO1), U4.22 (CE#)
~RAM0_U_CS: U3.18 (IO2), U5.22 (CE#)
~RAM1_L_CS: U3.17 (I03), U6.22 (CE#)
~RAM1_U_CS: U3.16 (IO4), U7.22 (CE#)
~RD_L: U4.24 (OE#), U6.24 (OE#), U8.24 (OE), U10.19 (IO1)
~RD_U: U5.24 (OE#), U7.24 (OE#), U9.24 (OE), U10.17 (I03), U13.21 (~RD)
~RESET: D2.2 (A), IC1.11 (B7), J5.2, J18.1, J28.53, JP8.1 (A), RN1.5 (R4), U1.18 (~RESET), U2.9, U26.39 (RESET)
~ROM_L_CS: U3.15 (IO5), U8.22 (CE)
~ROM_U_CS: U3.14 (IO6), U9.22 (CE)
~UART_CS: U11.18 (IO2), U13.14 (~CS2)
~UDS: J28.39, RN3.2 (R1), U1.7 (~UDS), U3.9 (I9), U10.3 (I3), U11.4 (I4), U18.K9 (~UDS/A0)
~VMA: J3.1, J28.48, RN1.6 (R5), U1.19 (~VMA)
~VPA: J3.3, RN1.7 (R6), U1.21 (~VPA), U12.19 (IO1)
~WR_L: JP1.1 (A), U4.29 (WE#), U6.29 (WE#), U10.18 (IO2)
~WR_U: JP2.1 (A), U5.29 (WE#), U7.29 (WE#), U10.16 (IO4), U13.18 (~WR)

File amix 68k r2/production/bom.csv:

Designator,Footprint,Quantity,Value,LCSC Part #
C1,CP_Radial_D5.0mm_P2.50mm,1,C_Polarized,
"C10, C11, C12, C13, C14, C15, C16, C17, C18, C21, C22, C23, C24, C25, C26, C27, C28, C29, C30, C31, C32, C8, C9",C_Rect_L4.0mm_W2.5mm_P2.50mm,23,100nF,
C19,CP_Radial_D5.0mm_P2.50mm,1,100uF,
C2,C_Rect_L4.0mm_W2.5mm_P2.50mm,1,1uF,
C20,CP_Radial_D6.3mm_P2.50mm,1,220uF,
"C3, C5, C7",CP_Radial_D5.0mm_P2.50mm,3,10uF,
"C33, C4, C6",CP_Radial_D5.0mm_P2.50mm,3,1uF,
"D1, D2",D_DO-35_SOD27_P7.62mm_Horizontal,2,D,
D10,LED_D4.0mm,1,LED_+5,
D11,LED_D4.0mm,1,LED_+5SB,
D12,LED_D4.0mm,1,LED_-12,
"D3, D4, D5, D6",LED_D4.0mm,4,LED,
"D7, D8",D_DO-35_SOD27_P7.62mm_Horizontal,2,1N4148,
D9,LED_D4.0mm,1,LED_+12,
"HOLE1, HOLE2, HOLE3, HOLE4, HOLE5, HOLE6, HOLE7",Hole_3mm,7,HOLE,
"IC1, IC2, IC3",DIP-20_W7.62mm_Socket_LongPads,3,74HCT245,
J1,PinHeader_1x03_P2.54mm_Vertical,1,BG,
J10,PinSocket_2x06_P2.54mm_Horizontal,1,PMOD_BOTTOM,
"J11, J12, J15, J27",PinHeader_1x04_P2.54mm_Vertical,4,Conn_01x04_Pin,
J13,PinHeader_1x07_P2.54mm_Vertical,1,RTC (SparkFun BOB-10160),
J14,USB_B_Lumberg_2411_02_Horizontal,1,USB_B,
J16,Molex_Mini-Fit_Jr_5566-24A2_2x12_P4.20mm_Vertical,1,ATX-24 - IF NO 12V in,
J17,BarrelJack_Horizontal,1,12V in if NO ATX,
J18,IDC-Header_2x20_P2.54mm_Vertical,1,IDE 40 pin,
J19,PinHeader_1x02_P2.54mm_Vertical,1,ExtPWRON,
J2,PinHeader_1x03_P2.54mm_Vertical,1,FCx,
J20,PinHeader_1x02_P2.54mm_Vertical,1,PWR_LED,
J21,IDC-Header_2x08_P2.54mm_Vertical,1,Conn_02x08_Odd_Even,
J22,PinHeader_1x12_P2.54mm_Vertical,1,PPI,
"J23, J24",PinHeader_1x08_P2.54mm_Vertical,2,Conn_01x08_Pin,
"J25, J26",PinHeader_2x04_P2.54mm_Vertical,2,Conn_02x04_Odd_Even,
J28,PinSocket_2x32_P2.54mm_Horizontal,1,Conn_02x32_Odd_Even,
J29,PinHeader_1x02_P2.54mm_Vertical,1,NMI,
J3,PinHeader_1x03_P2.54mm_Vertical,1,PRF,
J4,PinHeader_1x02_P2.54mm_Vertical,1,BUS_STAT,
J5,PinHeader_1x02_P2.54mm_Vertical,1,HLT and RESET,
J6,PinHeader_1x24_P2.54mm_Vertical,1,Upduino_LHS,
J7,PinHeader_1x24_P2.54mm_Vertical,1,Upduino_RHS,
J8,PinHeader_1x06_P2.54mm_Vertical,1,Conn_01x06_Pin,
J9,PinSocket_2x06_P2.54mm_Horizontal,1,PMOD_TOP,
"JP1, JP2, JP21, JP8",PinHeader_1x02_P2.54mm_Vertical,4,Jumper_2_Open,
"JP10, JP11",PinHeader_1x02_P2.54mm_Vertical,2,Close only if NO ATX,
"JP14, JP15",PinHeader_1x02_P2.54mm_Vertical,2,DTACK ctrl 0,
JP16,PinHeader_1x02_P2.54mm_Vertical,1,DMAAC_REQ0 = IDE,
JP17,PinHeader_1x02_P2.54mm_Vertical,1,DMAAC_ACK0 = IDE,
"JP18, JP20",PinHeader_1x02_P2.54mm_Vertical,2,Jumper_2_Bridged,
"JP3, JP4, JP5, JP6",PinHeader_1x02_P2.54mm_Vertical,4,Jumper,
"Q1, Q2",TO-92_Inline,2,2N3904,
"R1, R14, R15, R17, R2",R_Axial_DIN0207_L6.3mm_D2.5mm_P10.16mm_Horizontal,5,1k,
"R10, R11, R12, R5, R6, R7, R8, R9",R_Axial_DIN0207_L6.3mm_D2.5mm_P10.16mm_Horizontal,8,R,
"R13, R24",R_Axial_DIN0207_L6.3mm_D2.5mm_P10.16mm_Horizontal,2,150k,
"R16, R18, R19, R20, R21, R22, R3, R30, R4",R_Axial_DIN0207_L6.3mm_D2.5mm_P10.16mm_Horizontal,9,10k,
R23,R_Axial_DIN0207_L6.3mm_D2.5mm_P10.16mm_Horizontal,1,470,
"R25, R26",R_Axial_DIN0207_L6.3mm_D2.5mm_P10.16mm_Horizontal,2,680,
"R27, R28, R29",R_Axial_DIN0207_L6.3mm_D2.5mm_P10.16mm_Horizontal,3,330,
"RN1, RN2, RN3, RN4",R_Array_SIP8,4,R_Network07,
SW1,SW_PUSH_6mm,1,Reset,
SW3,SW_Slide_SPDT_Angled_CK_OS102011MA1Q,1,SW_SPDT,
U1,DIP-64_W22.86mm_Socket_LongPads,1,MC68010P,
"U10, U11, U12, U3",DIP-20_W7.62mm_Socket_LongPads,4,GAL16V8,
U13,DIP-40_W15.24mm_Socket_LongPads,1,16550,
U14,SSOP-28_5.3x10.2mm_P0.65mm,1,FT232RL,
U15,TO-220-3_Horizontal_TabDown,1,LM7805_TO220,
"U16, U28",DIP-14_W7.62mm_Socket_LongPads,2,74HC74,
U17,TO-220-3_Horizontal_TabDown,1,LM1117T-3.3,
U18,68 pin PGA socket 5108306810061101,1,~,
"U19, U20, U21",DIP-20_W7.62mm_Socket_LongPads,3,74HC245,
"U2, U27",DIP-14_W7.62mm_Socket_LongPads,2,74HC14,
"U22, U23",DIP-20_W7.62mm_Socket_LongPads,2,74HC373,
U24,DIP-14_W7.62mm_Socket_LongPads,1,74LS32,
U25,DIP-16_W7.62mm_Socket_LongPads,1,74LS148,
U26,DIP-48_W15.24mm_Socket_LongPads,1,68230,
"U4, U5, U6, U7",DIP-32_W15.24mm_Socket_LongPads,4,AS6C4008-55PCN,
"U8, U9",DIP_Socket-32_W11.9_W12.7_W15.24_W17.78_W18.5_3M_232-1285-00-0602J,2,SST39SF040,
Y1,Oscillator_DIP-14,1,1.8432Mhz,
Y3,Oscillator_DIP-14,1,12Mhz,
Y5,Oscillator_DIP-14,1,10Mhz,

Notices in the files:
xosera/xosera.kicad_pcb:
© Xark & Contributors
xosera/xosera.kicad_sch:
Copyright ©2021 Xark and Contributors
